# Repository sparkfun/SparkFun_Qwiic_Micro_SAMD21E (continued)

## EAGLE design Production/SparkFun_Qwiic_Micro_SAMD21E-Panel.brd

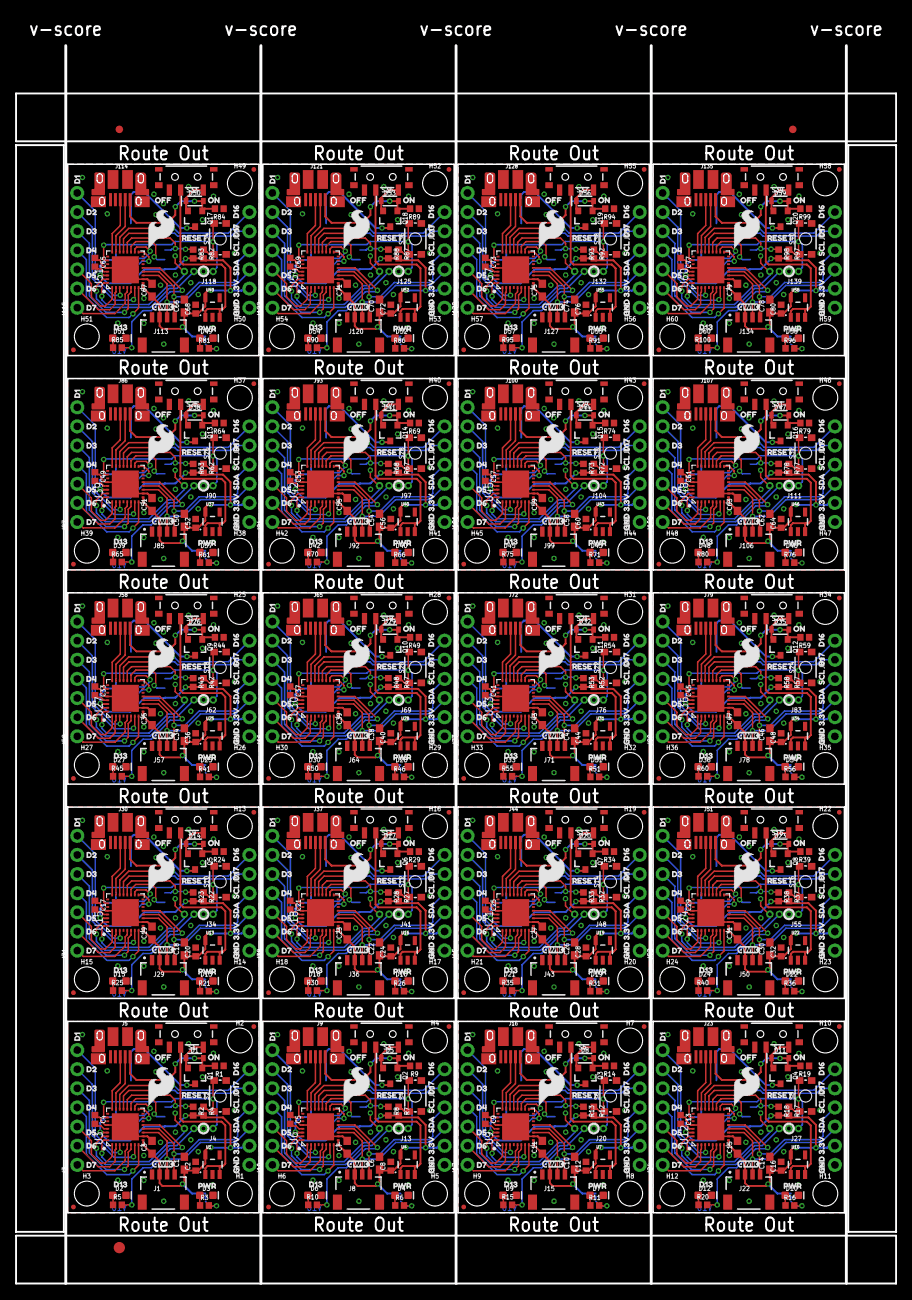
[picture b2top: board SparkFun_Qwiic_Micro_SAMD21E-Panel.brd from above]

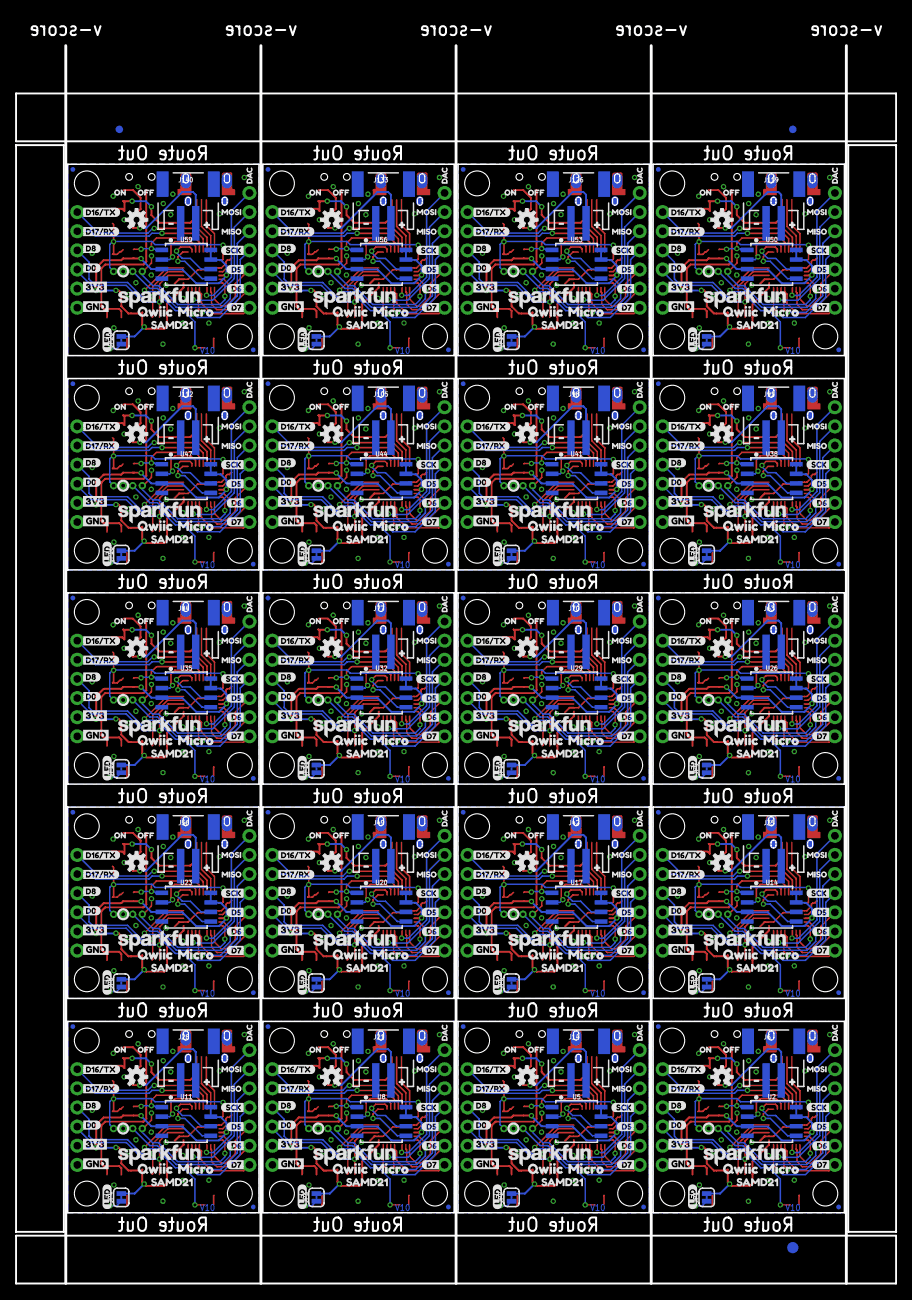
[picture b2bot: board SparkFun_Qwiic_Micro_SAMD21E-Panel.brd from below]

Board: 2 copper layers, 116.8 x 164.3 mm, 1586 parts (563 on the bottom side), 620 nets.

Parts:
C1, C3, C6, C7, C10, C11, C14, C15, C18, C19, C22, C23, C26, C27, C30, C31, C34, C35, C38, C39, C42, C43, C46, C47, C50, C51, C54, C55, C58, C59, C62, C63, C66, C67, C70, C71, C74, C75, C78, C79: 10uF; 0603
C2, C4, C5, C8, C9, C12, C13, C16, C17, C20, C21, C24, C25, C28, C29, C32, C33, C36, C37, C40, C41, C44, C45, C48, C49, C52, C53, C56, C57, C60, C61, C64, C65, C68, C69, C72, C73, C76, C77, C80: 1.0uF; 0402
D1, D5, D8, D11, D14, D17, D20, D23, D26, D29, D32, D35, D38, D41, D44, D47, D50, D53, D56, D59: 1A/23V/620mV; SOD-323
D2, D6, D9, D12, D15, D18, D21, D24, D27, D30, D33, D36, D39, D42, D45, D48, D51, D54, D57, D60: BLUE; LED-0603
D3, D4, D7, D10, D13, D16, D19, D22, D25, D28, D31, D34, D37, D40, D43, D46, D49, D52, D55, D58: RED; LED-0603
E$1, E$2, E$3, E$4: FIDUCIAL-1X2
E$5, E$6: FIDUCIAL-1.5X3
FD1, FD2, FD3, FD4, FD5, FD6, FD7, FD8, FD9, FD10, FD11, FD12, FD13, FD14, FD15, FD16, FD17, FD18, FD19, FD20, FD21, FD22, FD23, FD24, FD25, FD26, FD27, FD28, FD29, FD30, FD31, FD32, FD33, FD34, FD35, FD36, FD37, FD38, FD39, FD40, FD41, FD42, FD43, FD44, FD45, FD46, FD47, FD48, FD49, FD50, FD51, FD52, FD53, FD54, FD55, FD56, FD57, FD58, FD59, FD60, FD61, FD62, FD63, FD64, FD65, FD66, FD67, FD68, FD69, FD70, FD71, FD72, FD73, FD74, FD75, FD76, FD77, FD78, FD79, FD80: FIDUCIALUFIDUCIAL; FIDUCIAL-MICRO
H1, H2, H3, H4, H5, H6, H7, H8, H9, H10, H11, H12, H13, H14, H15, H16, H17, H18, H19, H20, H21, H22, H23, H24, H25, H26, H27, H28, H29, H30, H31, H32, H33, H34, H35, H36, H37, H38, H39, H40, H41, H42, H43, H44, H45, H46, H47, H48, H49, H50, H51, H52, H53, H54, H55, H56, H57, H58, H59, H60: STAND-OFF
J1, J8, J15, J22, J29, J36, J43, J50, J57, J64, J71, J78, J85, J92, J99, J106, J113, J120, J127, J134: JST04_1MM_RA
J2, J12, J19, J26, J33, J40, J47, J54, J61, J68, J75, J82, J89, J96, J103, J110, J117, J124, J131, J138: 1X04_NO_SILK
J3, J10, J17, J24, J31, J38, J45, J52, J59, J66, J73, J80, J87, J94, J101, J108, J115, J122, J129, J136: 1X07_NO_SILK
J4, J13, J20, J27, J34, J41, J48, J55, J62, J69, J76, J83, J90, J97, J104, J111, J118, J125, J132, J139: 1X04_1.27MM_NO_SILK
J5, J9, J16, J23, J30, J37, J44, J51, J58, J65, J72, J79, J86, J93, J100, J107, J114, J121, J128, J135: USB-MICROB-PTH-MILL
J6, J14, J21, J28, J35, J42, J49, J56, J63, J70, J77, J84, J91, J98, J105, J112, J119, J126, J133, J140: JST-2-SMD
J7, J11, J18, J25, J32, J39, J46, J53, J60, J67, J74, J81, J88, J95, J102, J109, J116, J123, J130, J137: 1X02_NO_SILK
JP1, JP2, JP3, JP4, JP5, JP6, JP7, JP8, JP9, JP10, JP11, JP12, JP13, JP14, JP15, JP16, JP17, JP18, JP19, JP20: LED; SMT-JUMPER_2_NC_TRACE_SILK
LOGO1, LOGO7, LOGO11, LOGO15, LOGO19, LOGO23, LOGO27, LOGO31, LOGO35, LOGO39, LOGO43, LOGO47, LOGO51, LOGO55, LOGO59, LOGO63, LOGO67, LOGO71, LOGO75, LOGO79: SFE_LOGO_NAME.1_INCH; SFE_LOGO_NAME_.1
LOGO2, LOGO6, LOGO10, LOGO14, LOGO18, LOGO22, LOGO26, LOGO30, LOGO34, LOGO38, LOGO42, LOGO46, LOGO50, LOGO54, LOGO58, LOGO62, LOGO66, LOGO70, LOGO74, LOGO78: SFE_LOGO_FLAME.2_INCH; SFE_LOGO_FLAME_.2
LOGO3, LOGO5, LOGO9, LOGO13, LOGO17, LOGO21, LOGO25, LOGO29, LOGO33, LOGO37, LOGO41, LOGO45, LOGO49, LOGO53, LOGO57, LOGO61, LOGO65, LOGO69, LOGO73, LOGO77: OSHW-LOGOS; OSHW-LOGO-S
LOGO4, LOGO8, LOGO12, LOGO16, LOGO20, LOGO24, LOGO28, LOGO32, LOGO36, LOGO40, LOGO44, LOGO48, LOGO52, LOGO56, LOGO60, LOGO64, LOGO68, LOGO72, LOGO76, LOGO80: QWIIC_LOGO_3MM; QWIIC_3MM
Q1, Q2, Q3, Q4, Q5, Q6, Q7, Q8, Q9, Q10, Q11, Q12, Q13, Q14, Q15, Q16, Q17, Q18, Q19, Q20: 3.1A/30V/105mΩ; SOT23-3
R1, R2, R4, R7, R8, R9, R12, R13, R14, R17, R18, R19, R22, R23, R24, R27, R28, R29, R32, R33, R34, R37, R38, R39, R42, R43, R44, R47, R48, R49, R52, R53, R54, R57, R58, R59, R62, R63, R64, R67, R68, R69, R72, R73, R74, R77, R78, R79, R82, R83, R84, R87, R88, R89, R92, R93, R94, R97, R98, R99: 10k; 0402
R3, R5, R6, R10, R11, R15, R16, R20, R21, R25, R26, R30, R31, R35, R36, R40, R41, R45, R46, R50, R51, R55, R56, R60, R61, R65, R66, R70, R71, R75, R76, R80, R81, R85, R86, R90, R91, R95, R96, R100: 1K; 0402
S1, S3, S5, S7, S9, S11, S13, S15, S17, S19, S21, S23, S25, S27, S29, S31, S33, S35, S37, S39: SWITCH_SPST_SMD_A
S2, S4, S6, S8, S10, S12, S14, S16, S18, S20, S22, S24, S26, S28, S30, S32, S34, S36, S38, S40: MOMENTARY-SWITCH-SPST-SMD-4.6X2.8MM; TACTILE_SWITCH_SMD_4.6X2.8MM
TP1, TP2, TP3, TP4, TP5, TP6, TP7, TP8, TP9, TP10, TP11, TP12, TP13, TP14, TP15, TP16, TP17, TP18, TP19, TP20, TP21, TP22, TP23, TP24, TP25, TP26, TP27, TP28, TP29, TP30, TP31, TP32, TP33, TP34, TP35, TP36, TP37, TP38, TP39, TP40, TP41, TP42, TP43, TP44, TP45, TP46, TP47, TP48, TP49, TP50, TP51, TP52, TP53, TP54, TP55, TP56, TP57, TP58, TP59, TP60: TEST-POINTTP_15TH_THRU; TP_15TH
U1, U4, U7, U10, U13, U16, U19, U22, U25, U28, U31, U34, U37, U40, U43, U46, U49, U52, U55, U58: 3.3V; SOT23-5
U2, U5, U8, U11, U14, U17, U20, U23, U26, U29, U32, U35, U38, U41, U44, U47, U50, U53, U56, U59: W25Q32FV; SOIC-8
U3, U6, U9, U12, U15, U18, U21, U24, U27, U30, U33, U36, U39, U42, U45, U48, U51, U54, U57, U60: ATSAMD21E18A-U; QFN-32_SAMD
U$1, U$59, U$98, U$137, U$176, U$215, U$254, U$293, U$332, U$371, U$410, U$449, U$488, U$527, U$566, U$605, U$644, U$683, U$722, U$761: D00
U$2, U$64, U$103, U$142, U$181, U$220, U$259, U$298, U$337, U$376, U$415, U$454, U$493, U$532, U$571, U$610, U$649, U$688, U$727, U$766: GND-03
U$3, U$30, U$79, U$118, U$157, U$196, U$235, U$274, U$313, U$352, U$391, U$430, U$469, U$508, U$547, U$586, U$625, U$664, U$703, U$742: #23
U$4, U$31, U$80, U$119, U$158, U$197, U$236, U$275, U$314, U$353, U$392, U$431, U$470, U$509, U$548, U$587, U$626, U$665, U$704, U$743: #24
U$5, U$32, U$81, U$120, U$159, U$198, U$237, U$276, U$315, U$354, U$393, U$432, U$471, U$510, U$549, U$588, U$627, U$666, U$705, U$744: 3#3V10
U$6, U$60, U$99, U$138, U$177, U$216, U$255, U$294, U$333, U$372, U$411, U$450, U$489, U$528, U$567, U$606, U$645, U$684, U$723, U$762: D12
U$7, U$70, U$109, U$148, U$187, U$226, U$265, U$304, U$343, U$382, U$421, U$460, U$499, U$538, U$577, U$616, U$655, U$694, U$733, U$772: D166
U$8, U$71, U$110, U$149, U$188, U$227, U$266, U$305, U$344, U$383, U$422, U$461, U$500, U$539, U$578, U$617, U$656, U$695, U$734, U$773: D177
U$9, U$72, U$111, U$150, U$189, U$228, U$267, U$306, U$345, U$384, U$423, U$462, U$501, U$540, U$579, U$618, U$657, U$696, U$735, U$774: D16#TX4
U$10, U$61, U$100, U$139, U$178, U$217, U$256, U$295, U$334, U$373, U$412, U$451, U$490, U$529, U$568, U$607, U$646, U$685, U$724, U$763: QWIIC2
U$11, U$73, U$112, U$151, U$190, U$229, U$268, U$307, U$346, U$385, U$424, U$463, U$502, U$541, U$580, U$619, U$658, U$697, U$736, U$775: D17#RX3
U$12, U$66, U$105, U$144, U$183, U$222, U$261, U$300, U$339, U$378, U$417, U$456, U$495, U$534, U$573, U$612, U$651, U$690, U$729, U$768: D75
U$13, U$67, U$106, U$145, U$184, U$223, U$262, U$301, U$340, U$379, U$418, U$457, U$496, U$535, U$574, U$613, U$652, U$691, U$730, U$769: DAC1
U$14, U$55, U$94, U$133, U$172, U$211, U$250, U$289, U$328, U$367, U$406, U$445, U$484, U$523, U$562, U$601, U$640, U$679, U$718, U$757: MISO0
U$15, U$63, U$102, U$141, U$180, U$219, U$258, U$297, U$336, U$375, U$414, U$453, U$492, U$531, U$570, U$609, U$648, U$687, U$726, U$765: SAMD213
U$16, U$68, U$107, U$146, U$185, U$224, U$263, U$302, U$341, U$380, U$419, U$458, U$497, U$536, U$575, U$614, U$653, U$692, U$731, U$770: MOSI2
U$17, U$65, U$104, U$143, U$182, U$221, U$260, U$299, U$338, U$377, U$416, U$455, U$494, U$533, U$572, U$611, U$650, U$689, U$728, U$767: 3V3-03
U$18, U$43, U$46, U$57, U$88, U$96, U$127, U$135, U$166, U$174, U$205, U$213, U$244, U$252, U$283, U$291, U$322, U$330, U$361, U$369, U$400, U$408, U$439, U$447, U$478, U$486, U$517, U$525, U$556, U$564, U$595, U$603, U$634, U$642, U$673, U$681, U$712, U$720, U$751, U$759: ON12
U$19, U$42, U$45, U$58, U$87, U$97, U$126, U$136, U$165, U$175, U$204, U$214, U$243, U$253, U$282, U$292, U$321, U$331, U$360, U$370, U$399, U$409, U$438, U$448, U$477, U$487, U$516, U$526, U$555, U$565, U$594, U$604, U$633, U$643, U$672, U$682, U$711, U$721, U$750, U$760: OFF13
U$20, U$54, U$93, U$132, U$171, U$210, U$249, U$288, U$327, U$366, U$405, U$444, U$483, U$522, U$561, U$600, U$639, U$678, U$717, U$756: SCK7
U$21, U$53, U$92, U$131, U$170, U$209, U$248, U$287, U$326, U$365, U$404, U$443, U$482, U$521, U$560, U$599, U$638, U$677, U$716, U$755: RESET0
U$22, U$74, U$113, U$152, U$191, U$230, U$269, U$308, U$347, U$386, U$425, U$464, U$503, U$542, U$581, U$620, U$659, U$698, U$737, U$776: D85
U$23, U$62, U$101, U$140, U$179, U$218, U$257, U$296, U$335, U$374, U$413, U$452, U$491, U$530, U$569, U$608, U$647, U$686, U$725, U$764: MICRO2
U$24, U$56, U$95, U$134, U$173, U$212, U$251, U$290, U$329, U$368, U$407, U$446, U$485, U$524, U$563, U$602, U$641, U$680, U$719, U$758: LED1
U$25, U$75, U$114, U$153, U$192, U$231, U$270, U$309, U$348, U$387, U$426, U$465, U$504, U$543, U$582, U$621, U$660, U$699, U$738, U$777: D50
U$26, U$76, U$115, U$154, U$193, U$232, U$271, U$310, U$349, U$388, U$427, U$466, U$505, U$544, U$583, U$622, U$661, U$700, U$739, U$778: D61
U$27, U$77, U$116, U$155, U$194, U$233, U$272, U$311, U$350, U$389, U$428, U$467, U$506, U$545, U$584, U$623, U$662, U$701, U$740, U$779: D72
U$28, U$69, U$108, U$147, U$186, U$225, U$264, U$303, U$342, U$381, U$420, U$459, U$498, U$537, U$576, U$615, U$654, U$693, U$732, U$771: D21
U$29, U$78, U$117, U$156, U$195, U$234, U$273, U$312, U$351, U$390, U$429, U$468, U$507, U$546, U$585, U$624, U$663, U$702, U$741, U$780: D136
U$33, U$36, U$82, U$121, U$160, U$199, U$238, U$277, U$316, U$355, U$394, U$433, U$472, U$511, U$550, U$589, U$628, U$667, U$706, U$745: D33
U$34, U$37, U$83, U$122, U$161, U$200, U$239, U$278, U$317, U$356, U$395, U$434, U$473, U$512, U$551, U$590, U$629, U$668, U$707, U$746: D41
U$35, U$38, U$84, U$123, U$162, U$201, U$240, U$279, U$318, U$357, U$396, U$435, U$474, U$513, U$552, U$591, U$630, U$669, U$708, U$747: D52
U$39, U$40, U$85, U$124, U$163, U$202, U$241, U$280, U$319, U$358, U$397, U$436, U$475, U$514, U$553, U$592, U$631, U$670, U$709, U$748: D65
U$41, U$44, U$86, U$125, U$164, U$203, U$242, U$281, U$320, U$359, U$398, U$437, U$476, U$515, U$554, U$593, U$632, U$671, U$710, U$749: GND11
U$47, U$48, U$89, U$128, U$167, U$206, U$245, U$284, U$323, U$362, U$401, U$440, U$479, U$518, U$557, U$596, U$635, U$674, U$713, U$752: PWR16
U$49, U$51, U$90, U$129, U$168, U$207, U$246, U$285, U$324, U$363, U$402, U$441, U$480, U$519, U$558, U$597, U$636, U$675, U$714, U$753: SCL8
U$50, U$52, U$91, U$130, U$169, U$208, U$247, U$286, U$325, U$364, U$403, U$442, U$481, U$520, U$559, U$598, U$637, U$676, U$715, U$754: SDA9

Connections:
3.3V: C1.1, C2.1, C3.1, J1.2, J2.2, JP1.2, R2.2, R4.2, U1.5, U2.3, U2.7, U2.8, U3.VDD, U3.VDDIN
3.3V1: C6.1, C7.1, C8.1, J8.2, J12.2, JP2.2, R7.2, R8.2, U4.5, U5.3, U5.7, U5.8, U6.VDD, U6.VDDIN
3.3V2: C10.1, C11.1, C12.1, J15.2, J19.2, JP3.2, R12.2, R13.2, U7.5, U8.3, U8.7, U8.8, U9.VDD, U9.VDDIN
3.3V3: C14.1, C15.1, C16.1, J22.2, J26.2, JP4.2, R17.2, R18.2, U10.5, U11.3, U11.7, U11.8, U12.VDD, U12.VDDIN
3.3V4: C18.1, C19.1, C20.1, J29.2, J33.2, JP5.2, R22.2, R23.2, U13.5, U14.3, U14.7, U14.8, U15.VDD, U15.VDDIN
3.3V5: C22.1, C23.1, C24.1, J36.2, J40.2, JP6.2, R27.2, R28.2, U16.5, U17.3, U17.7, U17.8, U18.VDD, U18.VDDIN
3.3V6: C26.1, C27.1, C28.1, J43.2, J47.2, JP7.2, R32.2, R33.2, U19.5, U20.3, U20.7, U20.8, U21.VDD, U21.VDDIN
3.3V7: C30.1, C31.1, C32.1, J50.2, J54.2, JP8.2, R37.2, R38.2, U22.5, U23.3, U23.7, U23.8, U24.VDD, U24.VDDIN
3.3V8: C34.1, C35.1, C36.1, J57.2, J61.2, JP9.2, R42.2, R43.2, U25.5, U26.3, U26.7, U26.8, U27.VDD, U27.VDDIN
3.3V9: C38.1, C39.1, C40.1, J64.2, J68.2, JP10.2, R47.2, R48.2, U28.5, U29.3, U29.7, U29.8, U30.VDD, U30.VDDIN
3.3V10: C42.1, C43.1, C44.1, J71.2, J75.2, JP11.2, R52.2, R53.2, U31.5, U32.3, U32.7, U32.8, U33.VDD, U33.VDDIN
3.3V11: C46.1, C47.1, C48.1, J78.2, J82.2, JP12.2, R57.2, R58.2, U34.5, U35.3, U35.7, U35.8, U36.VDD, U36.VDDIN
3.3V12: C50.1, C51.1, C52.1, J85.2, J89.2, JP13.2, R62.2, R63.2, U37.5, U38.3, U38.7, U38.8, U39.VDD, U39.VDDIN
3.3V13: C54.1, C55.1, C56.1, J92.2, J96.2, JP14.2, R67.2, R68.2, U40.5, U41.3, U41.7, U41.8, U42.VDD, U42.VDDIN
3.3V14: C58.1, C59.1, C60.1, J99.2, J103.2, JP15.2, R72.2, R73.2, U43.5, U44.3, U44.7, U44.8, U45.VDD, U45.VDDIN
3.3V15: C62.1, C63.1, C64.1, J106.2, J110.2, JP16.2, R77.2, R78.2, U46.5, U47.3, U47.7, U47.8, U48.VDD, U48.VDDIN
3.3V16: C66.1, C67.1, C68.1, J113.2, J117.2, JP17.2, R82.2, R83.2, U49.5, U50.3, U50.7, U50.8, U51.VDD, U51.VDDIN
3.3V17: C70.1, C71.1, C72.1, J120.2, J124.2, JP18.2, R87.2, R88.2, U52.5, U53.3, U53.7, U53.8, U54.VDD, U54.VDDIN
3.3V18: C74.1, C75.1, C76.1, J127.2, J131.2, JP19.2, R92.2, R93.2, U55.5, U56.3, U56.7, U56.8, U57.VDD, U57.VDDIN
3.3V19: C78.1, C79.1, C80.1, J134.2, J138.2, JP20.2, R97.2, R98.2, U58.5, U59.3, U59.7, U59.8, U60.VDD, U60.VDDIN
!RESET: J4.1, R4.1, S2.3, S2.4, U3.RES
!RESET1: J13.1, R7.1, S4.3, S4.4, U6.RES
!RESET2: J20.1, R12.1, S6.3, S6.4, U9.RES
!RESET3: J27.1, R17.1, S8.3, S8.4, U12.RES
!RESET4: J34.1, R22.1, S10.3, S10.4, U15.RES
!RESET5: J41.1, R27.1, S12.3, S12.4, U18.RES
!RESET6: J48.1, R32.1, S14.3, S14.4, U21.RES
!RESET7: J55.1, R37.1, S16.3, S16.4, U24.RES
!RESET8: J62.1, R42.1, S18.3, S18.4, U27.RES
!RESET9: J69.1, R47.1, S20.3, S20.4, U30.RES
!RESET10: J76.1, R52.1, S22.3, S22.4, U33.RES
!RESET11: J83.1, R57.1, S24.3, S24.4, U36.RES
!RESET12: J90.1, R62.1, S26.3, S26.4, U39.RES
!RESET13: J97.1, R67.1, S28.3, S28.4, U42.RES
!RESET14: J104.1, R72.1, S30.3, S30.4, U45.RES
!RESET15: J111.1, R77.1, S32.3, S32.4, U48.RES
!RESET16: J118.1, R82.1, S34.3, S34.4, U51.RES
!RESET17: J125.1, R87.1, S36.3, S36.4, U54.RES
!RESET18: J132.1, R92.1, S38.3, S38.4, U57.RES
!RESET19: J139.1, R97.1, S40.3, S40.4, U60.RES
D1: J10.1, U6.PA04
D2: J10.3, U6.PA00
D3: R10.2, U6.PA10
D4: J10.2, U6.PA01
D5: J3.3, U3.PA00
D6: J3.2, U3.PA01
D7: J3.1, U3.PA04
D8: J17.1, U9.PA04
D9: J17.3, U9.PA00
D10: R15.2, U9.PA10
D11: J17.2, U9.PA01
D12: J24.1, U12.PA04
D13: R5.2, U3.PA10
D14: J24.3, U12.PA00
D15: R20.2, U12.PA10
D16: J24.2, U12.PA01
D17: J31.1, U15.PA04
D18: J31.3, U15.PA00
D19: R25.2, U15.PA10
D20: J31.2, U15.PA01
D21: J38.1, U18.PA04
D22: J38.3, U18.PA00
D23: R30.2, U18.PA10
D24: J38.2, U18.PA01
D25: J45.1, U21.PA04
D26: J45.3, U21.PA00
D27: R35.2, U21.PA10
D28: J45.2, U21.PA01
D29: J52.1, U24.PA04
D30: J52.3, U24.PA00
D31: R40.2, U24.PA10
D32: J52.2, U24.PA01
D33: J59.1, U27.PA04
D34: J59.3, U27.PA00
D35: R45.2, U27.PA10
D36: J59.2, U27.PA01
D37: J66.1, U30.PA04
D38: J66.3, U30.PA00
D39: R50.2, U30.PA10
D40: J66.2, U30.PA01
D41: J73.1, U33.PA04
D42: J73.3, U33.PA00
D43: R55.2, U33.PA10
D44: J73.2, U33.PA01
D45: J80.1, U36.PA04
D46: J80.3, U36.PA00
D47: R60.2, U36.PA10
D48: J80.2, U36.PA01
D49: J87.1, U39.PA04
D50: J87.3, U39.PA00
D51: R65.2, U39.PA10
D52: J87.2, U39.PA01
D53: J94.1, U42.PA04
D54: J94.3, U42.PA00
D55: R70.2, U42.PA10
D56: J94.2, U42.PA01
D57: J101.1, U45.PA04
D58: J101.3, U45.PA00
D59: R75.2, U45.PA10
D60: J101.2, U45.PA01
D61: J108.1, U48.PA04
D62: J108.3, U48.PA00
D63: R80.2, U48.PA10
D64: J108.2, U48.PA01
D65: J115.1, U51.PA04
D66: J115.3, U51.PA00
D67: R85.2, U51.PA10
D68: J115.2, U51.PA01
D69: J122.1, U54.PA04
D70: J122.3, U54.PA00
D71: R90.2, U54.PA10
D72: J122.2, U54.PA01
D73: J129.1, U57.PA04
D74: J129.3, U57.PA00
D75: R95.2, U57.PA10
D76: J129.2, U57.PA01
D77: J136.1, U60.PA04
D78: J136.3, U60.PA00
D79: R100.2, U60.PA10
D80: J136.2, U60.PA01
D+: J5.D+, U3.PA25
D+1: J9.D+, U6.PA25
D+2: J16.D+, U9.PA25
D+3: J23.D+, U12.PA25
D+4: J30.D+, U15.PA25
D+5: J37.D+, U18.PA25
D+6: J44.D+, U21.PA25
D+7: J51.D+, U24.PA25
D+8: J58.D+, U27.PA25
D+9: J65.D+, U30.PA25
D+10: J72.D+, U33.PA25
D+11: J79.D+, U36.PA25
D+12: J86.D+, U39.PA25
D+13: J93.D+, U42.PA25
D+14: J100.D+, U45.PA25
D+15: J107.D+, U48.PA25
D+16: J114.D+, U51.PA25
D+17: J121.D+, U54.PA25
D+18: J128.D+, U57.PA25
D+19: J135.D+, U60.PA25
D-: J5.D-, U3.PA24
D-1: J9.D-, U6.PA24
D-2: J16.D-, U9.PA24
D-3: J23.D-, U12.PA24
D-4: J30.D-, U15.PA24
D-5: J37.D-, U18.PA24
D-6: J44.D-, U21.PA24
D-7: J51.D-, U24.PA24
D-8: J58.D-, U27.PA24
D-9: J65.D-, U30.PA24
D-10: J72.D-, U33.PA24
D-11: J79.D-, U36.PA24
D-12: J86.D-, U39.PA24
D-13: J93.D-, U42.PA24
D-14: J100.D-, U45.PA24
D-15: J107.D-, U48.PA24
D-16: J114.D-, U51.PA24
D-17: J121.D-, U54.PA24
D-18: J128.D-, U57.PA24
D-19: J135.D-, U60.PA24
DAC: J3.7, U3.PA02
DAC1: J10.7, U6.PA02
DAC2: J17.7, U9.PA02
DAC3: J24.7, U12.PA02
DAC4: J31.7, U15.PA02
DAC5: J38.7, U18.PA02
DAC6: J45.7, U21.PA02
DAC7: J52.7, U24.PA02
DAC8: J59.7, U27.PA02
DAC9: J66.7, U30.PA02
DAC10: J73.7, U33.PA02
DAC11: J80.7, U36.PA02
DAC12: J87.7, U39.PA02
DAC13: J94.7, U42.PA02
DAC14: J101.7, U45.PA02
DAC15: J108.7, U48.PA02
DAC16: J115.7, U51.PA02
DAC17: J122.7, U54.PA02
DAC18: J129.7, U57.PA02
DAC19: J136.7, U60.PA02
FLASH_CS: R2.1, U2.1, U3.PA19
FLASH_CS1: R8.1, U5.1, U6.PA19
FLASH_CS2: R13.1, U8.1, U9.PA19
FLASH_CS3: R18.1, U11.1, U12.PA19
FLASH_CS4: R23.1, U14.1, U15.PA19
FLASH_CS5: R28.1, U17.1, U18.PA19
FLASH_CS6: R33.1, U20.1, U21.PA19
FLASH_CS7: R38.1, U23.1, U24.PA19
FLASH_CS8: R43.1, U26.1, U27.PA19
FLASH_CS9: R48.1, U29.1, U30.PA19
FLASH_CS10: R53.1, U32.1, U33.PA19
FLASH_CS11: R58.1, U35.1, U36.PA19
FLASH_CS12: R63.1, U38.1, U39.PA19
FLASH_CS13: R68.1, U41.1, U42.PA19
FLASH_CS14: R73.1, U44.1, U45.PA19
FLASH_CS15: R78.1, U47.1, U48.PA19
FLASH_CS16: R83.1, U50.1, U51.PA19
FLASH_CS17: R88.1, U53.1, U54.PA19
FLASH_CS18: R93.1, U56.1, U57.PA19
FLASH_CS19: R98.1, U59.1, U60.PA19
FLASH_MISO: U2.2, U3.PA18
FLASH_MISO1: U5.2, U6.PA18
FLASH_MISO2: U8.2, U9.PA18
FLASH_MISO3: U11.2, U12.PA18
FLASH_MISO4: U14.2, U15.PA18
FLASH_MISO5: U17.2, U18.PA18
FLASH_MISO6: U20.2, U21.PA18
FLASH_MISO7: U23.2, U24.PA18
FLASH_MISO8: U26.2, U27.PA18
FLASH_MISO9: U29.2, U30.PA18
FLASH_MISO10: U32.2, U33.PA18
FLASH_MISO11: U35.2, U36.PA18
FLASH_MISO12: U38.2, U39.PA18
FLASH_MISO13: U41.2, U42.PA18
FLASH_MISO14: U44.2, U45.PA18
FLASH_MISO15: U47.2, U48.PA18
FLASH_MISO16: U50.2, U51.PA18
FLASH_MISO17: U53.2, U54.PA18
FLASH_MISO18: U56.2, U57.PA18
FLASH_MISO19: U59.2, U60.PA18
FLASH_MOSI: U2.5, U3.PA16
FLASH_MOSI1: U5.5, U6.PA16
FLASH_MOSI2: U8.5, U9.PA16
FLASH_MOSI3: U11.5, U12.PA16
FLASH_MOSI4: U14.5, U15.PA16
FLASH_MOSI5: U17.5, U18.PA16
FLASH_MOSI6: U20.5, U21.PA16
FLASH_MOSI7: U23.5, U24.PA16
FLASH_MOSI8: U26.5, U27.PA16
FLASH_MOSI9: U29.5, U30.PA16
FLASH_MOSI10: U32.5, U33.PA16
FLASH_MOSI11: U35.5, U36.PA16
FLASH_MOSI12: U38.5, U39.PA16
FLASH_MOSI13: U41.5, U42.PA16
FLASH_MOSI14: U44.5, U45.PA16
FLASH_MOSI15: U47.5, U48.PA16
FLASH_MOSI16: U50.5, U51.PA16
FLASH_MOSI17: U53.5, U54.PA16
FLASH_MOSI18: U56.5, U57.PA16
FLASH_MOSI19: U59.5, U60.PA16
FLASH_SCK: U2.6, U3.PA17
FLASH_SCK1: U5.6, U6.PA17
FLASH_SCK2: U8.6, U9.PA17
FLASH_SCK3: U11.6, U12.PA17
FLASH_SCK4: U14.6, U15.PA17
FLASH_SCK5: U17.6, U18.PA17
FLASH_SCK6: U20.6, U21.PA17
FLASH_SCK7: U23.6, U24.PA17
FLASH_SCK8: U26.6, U27.PA17
FLASH_SCK9: U29.6, U30.PA17
FLASH_SCK10: U32.6, U33.PA17
FLASH_SCK11: U35.6, U36.PA17
FLASH_SCK12: U38.6, U39.PA17
FLASH_SCK13: U41.6, U42.PA17
FLASH_SCK14: U44.6, U45.PA17
FLASH_SCK15: U47.6, U48.PA17
FLASH_SCK16: U50.6, U51.PA17
FLASH_SCK17: U53.6, U54.PA17
FLASH_SCK18: U56.6, U57.PA17
FLASH_SCK19: U59.6, U60.PA17
GND: C1.2, C2.2, C3.2, C4.1, D2.C, D3.C, J1.1, J2.1, J4.2, J5.GND, J5.SHIELD, J5.SHIELD2, J5.SHIELD3, J5.SHIELD4, J5.SHIELD5, J5.SHIELD6, J5.SHIELD7, J5.SHIELD8, J5.SHIELD9, J5.SHIELD10, J6.1, R1.1, S2.1, S2.2, U1.2, U2.4, U3.GND, U3.GNDANA, U3.PAD
GND1: C5.1, C6.2, C7.2, C8.2, D4.C, D6.C, J8.1, J9.GND, J9.SHIELD, J9.SHIELD2, J9.SHIELD3, J9.SHIELD4, J9.SHIELD5, J9.SHIELD6, J9.SHIELD7, J9.SHIELD8, J9.SHIELD9, J9.SHIELD10, J12.1, J13.2, J14.1, R9.1, S4.1, S4.2, U4.2, U5.4, U6.GND, U6.GNDANA, U6.PAD
GND2: C9.1, C10.2, C11.2, C12.2, D7.C, D9.C, J15.1, J16.GND, J16.SHIELD, J16.SHIELD2, J16.SHIELD3, J16.SHIELD4, J16.SHIELD5, J16.SHIELD6, J16.SHIELD7, J16.SHIELD8, J16.SHIELD9, J16.SHIELD10, J19.1, J20.2, J21.1, R14.1, S6.1, S6.2, U7.2, U8.4, U9.GND, U9.GNDANA, U9.PAD
GND3: C13.1, C14.2, C15.2, C16.2, D10.C, D12.C, J22.1, J23.GND, J23.SHIELD, J23.SHIELD2, J23.SHIELD3, J23.SHIELD4, J23.SHIELD5, J23.SHIELD6, J23.SHIELD7, J23.SHIELD8, J23.SHIELD9, J23.SHIELD10, J26.1, J27.2, J28.1, R19.1, S8.1, S8.2, U10.2, U11.4, U12.GND, U12.GNDANA, U12.PAD
GND4: C17.1, C18.2, C19.2, C20.2, D13.C, D15.C, J29.1, J30.GND, J30.SHIELD, J30.SHIELD2, J30.SHIELD3, J30.SHIELD4, J30.SHIELD5, J30.SHIELD6, J30.SHIELD7, J30.SHIELD8, J30.SHIELD9, J30.SHIELD10, J33.1, J34.2, J35.1, R24.1, S10.1, S10.2, U13.2, U14.4, U15.GND, U15.GNDANA, U15.PAD
GND5: C21.1, C22.2, C23.2, C24.2, D16.C, D18.C, J36.1, J37.GND, J37.SHIELD, J37.SHIELD2, J37.SHIELD3, J37.SHIELD4, J37.SHIELD5, J37.SHIELD6, J37.SHIELD7, J37.SHIELD8, J37.SHIELD9, J37.SHIELD10, J40.1, J41.2, J42.1, R29.1, S12.1, S12.2, U16.2, U17.4, U18.GND, U18.GNDANA, U18.PAD
GND6: C25.1, C26.2, C27.2, C28.2, D19.C, D21.C, J43.1, J44.GND, J44.SHIELD, J44.SHIELD2, J44.SHIELD3, J44.SHIELD4, J44.SHIELD5, J44.SHIELD6, J44.SHIELD7, J44.SHIELD8, J44.SHIELD9, J44.SHIELD10, J47.1, J48.2, J49.1, R34.1, S14.1, S14.2, U19.2, U20.4, U21.GND, U21.GNDANA, U21.PAD
GND7: C29.1, C30.2, C31.2, C32.2, D22.C, D24.C, J50.1, J51.GND, J51.SHIELD, J51.SHIELD2, J51.SHIELD3, J51.SHIELD4, J51.SHIELD5, J51.SHIELD6, J51.SHIELD7, J51.SHIELD8, J51.SHIELD9, J51.SHIELD10, J54.1, J55.2, J56.1, R39.1, S16.1, S16.2, U22.2, U23.4, U24.GND, U24.GNDANA, U24.PAD
GND8: C33.1, C34.2, C35.2, C36.2, D25.C, D27.C, J57.1, J58.GND, J58.SHIELD, J58.SHIELD2, J58.SHIELD3, J58.SHIELD4, J58.SHIELD5, J58.SHIELD6, J58.SHIELD7, J58.SHIELD8, J58.SHIELD9, J58.SHIELD10, J61.1, J62.2, J63.1, R44.1, S18.1, S18.2, U25.2, U26.4, U27.GND, U27.GNDANA, U27.PAD
GND9: C37.1, C38.2, C39.2, C40.2, D28.C, D30.C, J64.1, J65.GND, J65.SHIELD, J65.SHIELD2, J65.SHIELD3, J65.SHIELD4, J65.SHIELD5, J65.SHIELD6, J65.SHIELD7, J65.SHIELD8, J65.SHIELD9, J65.SHIELD10, J68.1, J69.2, J70.1, R49.1, S20.1, S20.2, U28.2, U29.4, U30.GND, U30.GNDANA, U30.PAD
GND10: C41.1, C42.2, C43.2, C44.2, D31.C, D33.C, J71.1, J72.GND, J72.SHIELD, J72.SHIELD2, J72.SHIELD3, J72.SHIELD4, J72.SHIELD5, J72.SHIELD6, J72.SHIELD7, J72.SHIELD8, J72.SHIELD9, J72.SHIELD10, J75.1, J76.2, J77.1, R54.1, S22.1, S22.2, U31.2, U32.4, U33.GND, U33.GNDANA, U33.PAD
GND11: C45.1, C46.2, C47.2, C48.2, D34.C, D36.C, J78.1, J79.GND, J79.SHIELD, J79.SHIELD2, J79.SHIELD3, J79.SHIELD4, J79.SHIELD5, J79.SHIELD6, J79.SHIELD7, J79.SHIELD8, J79.SHIELD9, J79.SHIELD10, J82.1, J83.2, J84.1, R59.1, S24.1, S24.2, U34.2, U35.4, U36.GND, U36.GNDANA, U36.PAD
GND12: C49.1, C50.2, C51.2, C52.2, D37.C, D39.C, J85.1, J86.GND, J86.SHIELD, J86.SHIELD2, J86.SHIELD3, J86.SHIELD4, J86.SHIELD5, J86.SHIELD6, J86.SHIELD7, J86.SHIELD8, J86.SHIELD9, J86.SHIELD10, J89.1, J90.2, J91.1, R64.1, S26.1, S26.2, U37.2, U38.4, U39.GND, U39.GNDANA, U39.PAD
GND13: C53.1, C54.2, C55.2, C56.2, D40.C, D42.C, J92.1, J93.GND, J93.SHIELD, J93.SHIELD2, J93.SHIELD3, J93.SHIELD4, J93.SHIELD5, J93.SHIELD6, J93.SHIELD7, J93.SHIELD8, J93.SHIELD9, J93.SHIELD10, J96.1, J97.2, J98.1, R69.1, S28.1, S28.2, U40.2, U41.4, U42.GND, U42.GNDANA, U42.PAD
GND14: C57.1, C58.2, C59.2, C60.2, D43.C, D45.C, J99.1, J100.GND, J100.SHIELD, J100.SHIELD2, J100.SHIELD3, J100.SHIELD4, J100.SHIELD5, J100.SHIELD6, J100.SHIELD7, J100.SHIELD8, J100.SHIELD9, J100.SHIELD10, J103.1, J104.2, J105.1, R74.1, S30.1, S30.2, U43.2, U44.4, U45.GND, U45.GNDANA, U45.PAD
GND15: C61.1, C62.2, C63.2, C64.2, D46.C, D48.C, J106.1, J107.GND, J107.SHIELD, J107.SHIELD2, J107.SHIELD3, J107.SHIELD4, J107.SHIELD5, J107.SHIELD6, J107.SHIELD7, J107.SHIELD8, J107.SHIELD9, J107.SHIELD10, J110.1, J111.2, J112.1, R79.1, S32.1, S32.2, U46.2, U47.4, U48.GND, U48.GNDANA, U48.PAD
GND16: C65.1, C66.2, C67.2, C68.2, D49.C, D51.C, J113.1, J114.GND, J114.SHIELD, J114.SHIELD2, J114.SHIELD3, J114.SHIELD4, J114.SHIELD5, J114.SHIELD6, J114.SHIELD7, J114.SHIELD8, J114.SHIELD9, J114.SHIELD10, J117.1, J118.2, J119.1, R84.1, S34.1, S34.2, U49.2, U50.4, U51.GND, U51.GNDANA, U51.PAD
GND17: C69.1, C70.2, C71.2, C72.2, D52.C, D54.C, J120.1, J121.GND, J121.SHIELD, J121.SHIELD2, J121.SHIELD3, J121.SHIELD4, J121.SHIELD5, J121.SHIELD6, J121.SHIELD7, J121.SHIELD8, J121.SHIELD9, J121.SHIELD10, J124.1, J125.2, J126.1, R89.1, S36.1, S36.2, U52.2, U53.4, U54.GND, U54.GNDANA, U54.PAD
GND18: C73.1, C74.2, C75.2, C76.2, D55.C, D57.C, J127.1, J128.GND, J128.SHIELD, J128.SHIELD2, J128.SHIELD3, J128.SHIELD4, J128.SHIELD5, J128.SHIELD6, J128.SHIELD7, J128.SHIELD8, J128.SHIELD9, J128.SHIELD10, J131.1, J132.2, J133.1, R94.1, S38.1, S38.2, U55.2, U56.4, U57.GND, U57.GNDANA, U57.PAD
GND19: C77.1, C78.2, C79.2, C80.2, D58.C, D60.C, J134.1, J135.GND, J135.SHIELD, J135.SHIELD2, J135.SHIELD3, J135.SHIELD4, J135.SHIELD5, J135.SHIELD6, J135.SHIELD7, J135.SHIELD8, J135.SHIELD9, J135.SHIELD10, J138.1, J139.2, J140.1, R99.1, S40.1, S40.2, U58.2, U59.4, U60.GND, U60.GNDANA, U60.PAD
MISO: J3.5, U3.PA05
MISO1: J10.5, U6.PA05
MISO2: J17.5, U9.PA05
MISO3: J24.5, U12.PA05
MISO4: J31.5, U15.PA05
MISO5: J38.5, U18.PA05
MISO6: J45.5, U21.PA05
MISO7: J52.5, U24.PA05
MISO8: J59.5, U27.PA05
MISO9: J66.5, U30.PA05
MISO10: J73.5, U33.PA05
MISO11: J80.5, U36.PA05
MISO12: J87.5, U39.PA05
MISO13: J94.5, U42.PA05
MISO14: J101.5, U45.PA05
MISO15: J108.5, U48.PA05
MISO16: J115.5, U51.PA05
MISO17: J122.5, U54.PA05
MISO18: J129.5, U57.PA05
MISO19: J136.5, U60.PA05
MOSI: J3.6, U3.PA06
MOSI1: J10.6, U6.PA06
MOSI2: J17.6, U9.PA06
MOSI3: J24.6, U12.PA06
MOSI4: J31.6, U15.PA06
MOSI5: J38.6, U18.PA06
MOSI6: J45.6, U21.PA06
MOSI7: J52.6, U24.PA06
MOSI8: J59.6, U27.PA06
MOSI9: J66.6, U30.PA06
MOSI10: J73.6, U33.PA06
MOSI11: J80.6, U36.PA06
MOSI12: J87.6, U39.PA06
MOSI13: J94.6, U42.PA06
MOSI14: J101.6, U45.PA06
MOSI15: J108.6, U48.PA06
MOSI16: J115.6, U51.PA06
MOSI17: J122.6, U54.PA06
MOSI18: J129.6, U57.PA06
MOSI19: J136.6, U60.PA06
unnamed: D3.A, R3.1
unnamed: JP1.1, R3.2
unnamed: D4.A, R6.1
unnamed: D2.A, R5.1
unnamed: JP2.1, R6.2
unnamed: D6.A, R10.1
unnamed: D7.A, R11.1
unnamed: JP3.1, R11.2
unnamed: D9.A, R15.1
unnamed: D10.A, R16.1
unnamed: JP4.1, R16.2
unnamed: D12.A, R20.1
unnamed: D13.A, R21.1
unnamed: JP5.1, R21.2
unnamed: D15.A, R25.1
unnamed: D16.A, R26.1
unnamed: JP6.1, R26.2
unnamed: D18.A, R30.1
unnamed: D19.A, R31.1
unnamed: JP7.1, R31.2
unnamed: D21.A, R35.1
unnamed: D22.A, R36.1
unnamed: JP8.1, R36.2
unnamed: D24.A, R40.1
unnamed: D25.A, R41.1
unnamed: JP9.1, R41.2
unnamed: D27.A, R45.1
unnamed: D28.A, R46.1
unnamed: JP10.1, R46.2
unnamed: D30.A, R50.1
unnamed: D31.A, R51.1
unnamed: JP11.1, R51.2
unnamed: D33.A, R55.1
unnamed: D34.A, R56.1
unnamed: JP12.1, R56.2
unnamed: D36.A, R60.1
unnamed: D37.A, R61.1
unnamed: JP13.1, R61.2
unnamed: D39.A, R65.1
unnamed: D40.A, R66.1
unnamed: JP14.1, R66.2
unnamed: D42.A, R70.1
unnamed: D43.A, R71.1
unnamed: JP15.1, R71.2
unnamed: D45.A, R75.1
unnamed: D46.A, R76.1
unnamed: JP16.1, R76.2
unnamed: D48.A, R80.1
unnamed: D49.A, R81.1
unnamed: JP17.1, R81.2
unnamed: D51.A, R85.1
unnamed: D52.A, R86.1
unnamed: JP18.1, R86.2
unnamed: D54.A, R90.1
unnamed: D55.A, R91.1
unnamed: JP19.1, R91.2
unnamed: D57.A, R95.1
unnamed: D58.A, R96.1
unnamed: JP20.1, R96.2
unnamed: D60.A, R100.1
RX: J7.2, U3.PA23
RX1: J11.2, U6.PA23
RX2: J18.2, U9.PA23
RX3: J25.2, U12.PA23
RX4: J32.2, U15.PA23
RX5: J39.2, U18.PA23
RX6: J46.2, U21.PA23
RX7: J53.2, U24.PA23
RX8: J60.2, U27.PA23
RX9: J67.2, U30.PA23
RX10: J74.2, U33.PA23
RX11: J81.2, U36.PA23
RX12: J88.2, U39.PA23
RX13: J95.2, U42.PA23
RX14: J102.2, U45.PA23
RX15: J109.2, U48.PA23
RX16: J116.2, U51.PA23
RX17: J123.2, U54.PA23
RX18: J130.2, U57.PA23
RX19: J137.2, U60.PA23
SCK: J3.4, U3.PA07
SCK1: J10.4, U6.PA07
SCK2: J17.4, U9.PA07
SCK3: J24.4, U12.PA07
SCK4: J31.4, U15.PA07
SCK5: J38.4, U18.PA07
SCK6: J45.4, U21.PA07
SCK7: J52.4, U24.PA07
SCK8: J59.4, U27.PA07
SCK9: J66.4, U30.PA07
SCK10: J73.4, U33.PA07
SCK11: J80.4, U36.PA07
SCK12: J87.4, U39.PA07
SCK13: J94.4, U42.PA07
SCK14: J101.4, U45.PA07
SCK15: J108.4, U48.PA07
SCK16: J115.4, U51.PA07
SCK17: J122.4, U54.PA07
SCK18: J129.4, U57.PA07
SCK19: J136.4, U60.PA07
SCL: J1.4, J2.4, U3.PA09
SCL1: J8.4, J12.4, U6.PA09
SCL2: J15.4, J19.4, U9.PA09
SCL3: J22.4, J26.4, U12.PA09
SCL4: J29.4, J33.4, U15.PA09
SCL5: J36.4, J40.4, U18.PA09
SCL6: J43.4, J47.4, U21.PA09
SCL7: J50.4, J54.4, U24.PA09
SCL8: J57.4, J61.4, U27.PA09
SCL9: J64.4, J68.4, U30.PA09
SCL10: J71.4, J75.4, U33.PA09
SCL11: J78.4, J82.4, U36.PA09
SCL12: J85.4, J89.4, U39.PA09
SCL13: J92.4, J96.4, U42.PA09
SCL14: J99.4, J103.4, U45.PA09
SCL15: J106.4, J110.4, U48.PA09
SCL16: J113.4, J117.4, U51.PA09
SCL17: J120.4, J124.4, U54.PA09
SCL18: J127.4, J131.4, U57.PA09
SCL19: J134.4, J138.4, U60.PA09
SDA: J1.3, J2.3, U3.PA08
SDA1: J8.3, J12.3, U6.PA08
SDA2: J15.3, J19.3, U9.PA08
SDA3: J22.3, J26.3, U12.PA08
SDA4: J29.3, J33.3, U15.PA08
SDA5: J36.3, J40.3, U18.PA08
SDA6: J43.3, J47.3, U21.PA08
SDA7: J50.3, J54.3, U24.PA08
SDA8: J57.3, J61.3, U27.PA08
SDA9: J64.3, J68.3, U30.PA08
SDA10: J71.3, J75.3, U33.PA08
SDA11: J78.3, J82.3, U36.PA08
SDA12: J85.3, J89.3, U39.PA08
SDA13: J92.3, J96.3, U42.PA08
SDA14: J99.3, J103.3, U45.PA08
SDA15: J106.3, J110.3, U48.PA08
SDA16: J113.3, J117.3, U51.PA08
SDA17: J120.3, J124.3, U54.PA08
SDA18: J127.3, J131.3, U57.PA08
SDA19: J134.3, J138.3, U60.PA08
SWCLK: J4.3, U3.PA30
SWCLK1: J13.3, U6.PA30
SWCLK2: J20.3, U9.PA30
SWCLK3: J27.3, U12.PA30
SWCLK4: J34.3, U15.PA30
SWCLK5: J41.3, U18.PA30
SWCLK6: J48.3, U21.PA30
SWCLK7: J55.3, U24.PA30
SWCLK8: J62.3, U27.PA30
SWCLK9: J69.3, U30.PA30
SWCLK10: J76.3, U33.PA30
SWCLK11: J83.3, U36.PA30
SWCLK12: J90.3, U39.PA30
SWCLK13: J97.3, U42.PA30
SWCLK14: J104.3, U45.PA30
SWCLK15: J111.3, U48.PA30
SWCLK16: J118.3, U51.PA30
SWCLK17: J125.3, U54.PA30
SWCLK18: J132.3, U57.PA30
SWCLK19: J139.3, U60.PA30
SWDIO: J4.4, TP3.P$1, U3.PA31
SWDIO1: J13.4, TP5.P$1, U6.PA31
SWDIO2: J20.4, TP8.P$1, U9.PA31
SWDIO3: J27.4, TP11.P$1, U12.PA31
SWDIO4: J34.4, TP14.P$1, U15.PA31
SWDIO5: J41.4, TP17.P$1, U18.PA31
SWDIO6: J48.4, TP20.P$1, U21.PA31
SWDIO7: J55.4, TP23.P$1, U24.PA31
SWDIO8: J62.4, TP26.P$1, U27.PA31
SWDIO9: J69.4, TP29.P$1, U30.PA31
SWDIO10: J76.4, TP32.P$1, U33.PA31
SWDIO11: J83.4, TP35.P$1, U36.PA31
SWDIO12: J90.4, TP38.P$1, U39.PA31
SWDIO13: J97.4, TP41.P$1, U42.PA31
SWDIO14: J104.4, TP44.P$1, U45.PA31
SWDIO15: J111.4, TP47.P$1, U48.PA31
SWDIO16: J118.4, TP50.P$1, U51.PA31
SWDIO17: J125.4, TP53.P$1, U54.PA31
SWDIO18: J132.4, TP56.P$1, U57.PA31
SWDIO19: J139.4, TP59.P$1, U60.PA31
TX: J7.1, U3.PA22
TX1: J11.1, U6.PA22
TX2: J18.1, U9.PA22
TX3: J25.1, U12.PA22
TX4: J32.1, U15.PA22
TX5: J39.1, U18.PA22
TX6: J46.1, U21.PA22
TX7: J53.1, U24.PA22
TX8: J60.1, U27.PA22
TX9: J67.1, U30.PA22
TX10: J74.1, U33.PA22
TX11: J81.1, U36.PA22
TX12: J88.1, U39.PA22
TX13: J95.1, U42.PA22
TX14: J102.1, U45.PA22
TX15: J109.1, U48.PA22
TX16: J116.1, U51.PA22
TX17: J123.1, U54.PA22
TX18: J130.1, U57.PA22
TX19: J137.1, U60.PA22
VDDCORE: C4.2, U3.VDDCORE
VDDCORE1: C5.2, U6.VDDCORE
VDDCORE2: C9.2, U9.VDDCORE
VDDCORE3: C13.2, U12.VDDCORE
VDDCORE4: C17.2, U15.VDDCORE
VDDCORE5: C21.2, U18.VDDCORE
VDDCORE6: C25.2, U21.VDDCORE
VDDCORE7: C29.2, U24.VDDCORE
VDDCORE8: C33.2, U27.VDDCORE
VDDCORE9: C37.2, U30.VDDCORE
VDDCORE10: C41.2, U33.VDDCORE
VDDCORE11: C45.2, U36.VDDCORE
VDDCORE12: C49.2, U39.VDDCORE
VDDCORE13: C53.2, U42.VDDCORE
VDDCORE14: C57.2, U45.VDDCORE
VDDCORE15: C61.2, U48.VDDCORE
VDDCORE16: C65.2, U51.VDDCORE
VDDCORE17: C69.2, U54.VDDCORE
VDDCORE18: C73.2, U57.VDDCORE
VDDCORE19: C77.2, U60.VDDCORE
VIN: S1.2, U1.1, U1.3
VIN1: D1.C, Q1.2, S1.3
VIN2: S3.2, U4.1, U4.3
VIN3: D5.C, Q2.2, S3.3
VIN4: S5.2, U7.1, U7.3
VIN5: D8.C, Q3.2, S5.3
VIN6: S7.2, U10.1, U10.3
VIN7: D11.C, Q4.2, S7.3
VIN8: S9.2, U13.1, U13.3
VIN9: D14.C, Q5.2, S9.3
VIN10: S11.2, U16.1, U16.3
VIN11: D17.C, Q6.2, S11.3
VIN12: S13.2, U19.1, U19.3
VIN13: D20.C, Q7.2, S13.3
VIN14: S15.2, U22.1, U22.3
VIN15: D23.C, Q8.2, S15.3
VIN16: S17.2, U25.1, U25.3
VIN17: D26.C, Q9.2, S17.3
VIN18: S19.2, U28.1, U28.3
VIN19: D29.C, Q10.2, S19.3
VIN20: S21.2, U31.1, U31.3
VIN21: D32.C, Q11.2, S21.3
VIN22: S23.2, U34.1, U34.3
VIN23: D35.C, Q12.2, S23.3
VIN24: S25.2, U37.1, U37.3
VIN25: D38.C, Q13.2, S25.3
VIN26: S27.2, U40.1, U40.3
VIN27: D41.C, Q14.2, S27.3
VIN28: S29.2, U43.1, U43.3
VIN29: D44.C, Q15.2, S29.3
VIN30: S31.2, U46.1, U46.3
VIN31: D47.C, Q16.2, S31.3
VIN32: S33.2, U49.1, U49.3
VIN33: D50.C, Q17.2, S33.3
VIN34: S35.2, U52.1, U52.3
VIN35: D53.C, Q18.2, S35.3
VIN36: S37.2, U55.1, U55.3
VIN37: D56.C, Q19.2, S37.3
VIN38: S39.2, U58.1, U58.3
VIN39: D59.C, Q20.2, S39.3
V_BATT: J6.2, Q1.3, TP2.P$1
V_BATT1: J14.2, Q2.3, TP6.P$1
V_BATT2: J21.2, Q3.3, TP9.P$1
V_BATT3: J28.2, Q4.3, TP12.P$1
V_BATT4: J35.2, Q5.3, TP15.P$1
V_BATT5: J42.2, Q6.3, TP18.P$1
V_BATT6: J49.2, Q7.3, TP21.P$1
V_BATT7: J56.2, Q8.3, TP24.P$1
V_BATT8: J63.2, Q9.3, TP27.P$1
V_BATT9: J70.2, Q10.3, TP30.P$1
V_BATT10: J77.2, Q11.3, TP33.P$1
V_BATT11: J84.2, Q12.3, TP36.P$1
V_BATT12: J91.2, Q13.3, TP39.P$1
V_BATT13: J98.2, Q14.3, TP42.P$1
V_BATT14: J105.2, Q15.3, TP45.P$1
V_BATT15: J112.2, Q16.3, TP48.P$1
V_BATT16: J119.2, Q17.3, TP51.P$1
V_BATT17: J126.2, Q18.3, TP54.P$1
V_BATT18: J133.2, Q19.3, TP57.P$1
V_BATT19: J140.2, Q20.3, TP60.P$1
V_USB: D1.A, J5.VBUS, Q1.1, R1.2, TP1.P$1
V_USB1: D5.A, J9.VBUS, Q2.1, R9.2, TP4.P$1
V_USB2: D8.A, J16.VBUS, Q3.1, R14.2, TP7.P$1
V_USB3: D11.A, J23.VBUS, Q4.1, R19.2, TP10.P$1
V_USB4: D14.A, J30.VBUS, Q5.1, R24.2, TP13.P$1
V_USB5: D17.A, J37.VBUS, Q6.1, R29.2, TP16.P$1
V_USB6: D20.A, J44.VBUS, Q7.1, R34.2, TP19.P$1
V_USB7: D23.A, J51.VBUS, Q8.1, R39.2, TP22.P$1
V_USB8: D26.A, J58.VBUS, Q9.1, R44.2, TP25.P$1
V_USB9: D29.A, J65.VBUS, Q10.1, R49.2, TP28.P$1
V_USB10: D32.A, J72.VBUS, Q11.1, R54.2, TP31.P$1
V_USB11: D35.A, J79.VBUS, Q12.1, R59.2, TP34.P$1
V_USB12: D38.A, J86.VBUS, Q13.1, R64.2, TP37.P$1
V_USB13: D41.A, J93.VBUS, Q14.1, R69.2, TP40.P$1
V_USB14: D44.A, J100.VBUS, Q15.1, R74.2, TP43.P$1
V_USB15: D47.A, J107.VBUS, Q16.1, R79.2, TP46.P$1
V_USB16: D50.A, J114.VBUS, Q17.1, R84.2, TP49.P$1
V_USB17: D53.A, J121.VBUS, Q18.1, R89.2, TP52.P$1
V_USB18: D56.A, J128.VBUS, Q19.1, R94.2, TP55.P$1
V_USB19: D59.A, J135.VBUS, Q20.1, R99.2, TP58.P$1
